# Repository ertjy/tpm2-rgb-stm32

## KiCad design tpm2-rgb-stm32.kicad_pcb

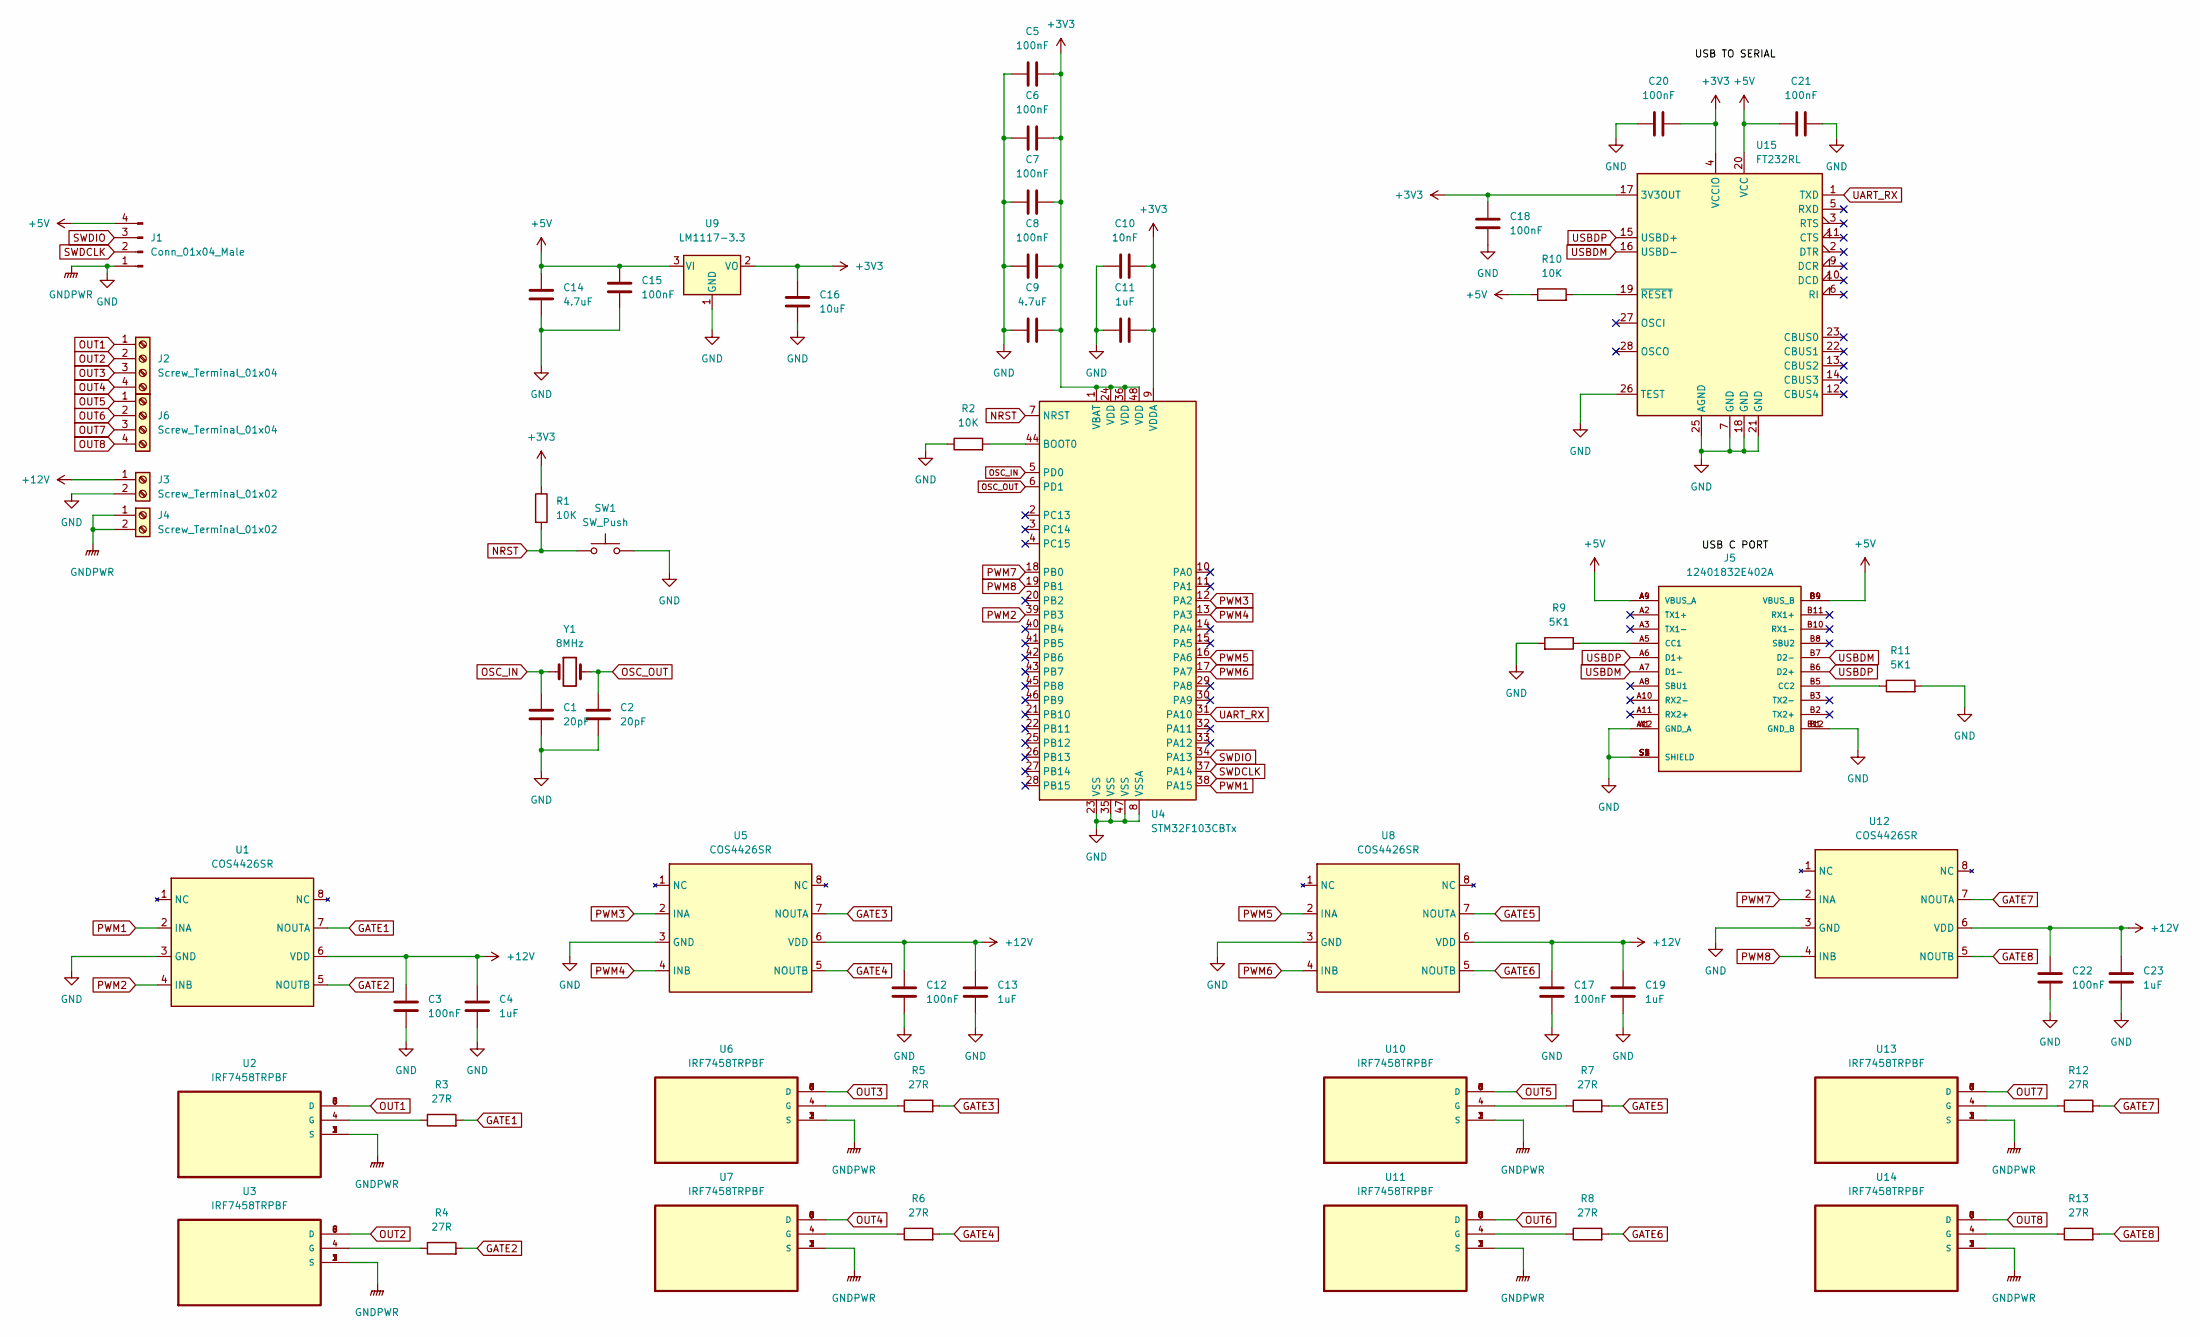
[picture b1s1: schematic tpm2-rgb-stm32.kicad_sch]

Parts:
C1, C2: 20pF; C_0805_2012Metric
C3, C5, C6, C7, C8, C12, C15, C17, C18, C20, C21, C22: 100nF; C_0805_2012Metric
C4, C11, C13, C19, C23: 1uF; C_0805_2012Metric
C9, C14: 4.7uF; C_0805_2012Metric
C10: 10nF; C_0805_2012Metric
C16: 10uF; C_0805_2012Metric
J1: Conn_01x04_Male; PinHeader_1x04_P2.54mm_Vertical
J2, J6: Screw_Terminal_01x04; TerminalBlock_bornier-4_P5.08mm
J3, J4: Screw_Terminal_01x02; TerminalBlock_bornier-2_P5.08mm
J5: 12401832E402A; AMPHENOL_12401832E402A; PARTREV X2
R1, R2, R10: 10K; R_0805_2012Metric
R3, R4, R5, R6, R7, R8, R12, R13: 27R; R_0805_2012Metric
R9, R11: 5K1; R_0805_2012Metric
SW1: SW_Push; SW_147873-1
U1, U5, U8, U12: COS4426SR; SO-8_3.9x4.9mm_P1.27mm
U2, U3, U6, U7, U10, U11, U13, U14: IRF7458TRPBF; SOIC127P490X600X175-8N
U4: STM32F103CBTx; LQFP-48_7x7mm_P0.5mm
U9: LM1117-3.3; SOT-223-3_TabPin2
U15: FT232RL; SSOP-28_5.3x10.2mm_P0.65mm
Y1: 8MHz; Crystal_SMD_HC49-SD

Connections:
+3V3: C5.2, C6.2, C7.2, C8.2, C9.2, C10.2, C11.2, C16.1, C18.1, C20.2, R1.1, U4.1 (VBAT), U4.9 (VDDA), U4.24 (VDD), U4.36 (VDD), U4.48 (VDD), U9.2 (VO), U15.4 (VCCIO), U15.17 (3V3OUT)
+5V: C14.1, C15.1, C21.1, J1.4, J5.A4 (VBUS_A), J5.A9 (VBUS_A), J5.B4 (VBUS_B), J5.B9 (VBUS_B), R10.1, U9.3 (VI), U15.20 (VCC)
+12V: C3.1, C4.1, C12.1, C13.1, C17.1, C19.1, C22.1, C23.1, J3.1, U1.6 (VDD), U5.6 (VDD), U8.6 (VDD), U12.6 (VDD)
GATE1: R3.2, U1.7 (NOUTA)
GATE2: R4.2, U1.5 (NOUTB)
GATE3: R5.2, U5.7 (NOUTA)
GATE4: R6.2, U5.5 (NOUTB)
GATE5: R7.2, U8.7 (NOUTA)
GATE6: R8.2, U8.5 (NOUTB)
GATE7: R12.2, U12.7 (NOUTA)
GATE8: R13.2, U12.5 (NOUTB)
GND: C1.2, C2.2, C3.2, C4.2, C5.1, C6.1, C7.1, C8.1, C9.1, C10.1, C11.1, C12.2, C13.2, C14.2, C15.2, C16.2, C17.2, C18.2, C19.2, C20.1, C21.2, C22.2, C23.2, J1.1, J3.2, J4.1, J4.2, J5.A1 (GND_A), J5.A12 (GND_A), J5.B1 (GND_B), J5.B12 (GND_B), J5.S1 (SHIELD), J5.S2 (SHIELD), J5.S3 (SHIELD), J5.S4 (SHIELD), R2.1, R9.2, R11.2, SW1.2, U1.3 (GND), U2.1 (S), U2.2 (S), U2.3 (S), U3.1 (S), U3.2 (S), U3.3 (S), U4.8 (VSSA), U4.23 (VSS), U4.35 (VSS), U4.47 (VSS), U5.3 (GND), U6.1 (S), U6.2 (S), U6.3 (S), U7.1 (S), U7.2 (S), U7.3 (S), U8.3 (GND), U9.1 (GND), U10.1 (S), U10.2 (S), U10.3 (S), U11.1 (S), U11.2 (S), U11.3 (S), U12.3 (GND), U13.1 (S), U13.2 (S), U13.3 (S), U14.1 (S), U14.2 (S), U14.3 (S), U15.7 (GND), U15.18 (GND), U15.21 (GND), U15.25 (AGND), U15.26 (TEST)
NRST: R1.2, SW1.1, U4.7 (NRST)
unnamed: J5.A5 (CC1), R9.1
unnamed: J5.B5 (CC2), R11.1
unnamed: R2.2, U4.44 (BOOT0)
unnamed: R3.1, U2.4 (G)
unnamed: R4.1, U3.4 (G)
unnamed: R5.1, U6.4 (G)
unnamed: R6.1, U7.4 (G)
unnamed: R7.1, U10.4 (G)
unnamed: R8.1, U11.4 (G)
unnamed: R10.2, U15.19 (~RESET)
unnamed: R12.1, U13.4 (G)
unnamed: R13.1, U14.4 (G)
OSC_IN: C1.1, U4.5 (PD0), Y1.1
OSC_OUT: C2.1, U4.6 (PD1), Y1.2
OUT1: J2.1, U2.5 (D), U2.6 (D), U2.7 (D), U2.8 (D)
OUT2: J2.2, U3.5 (D), U3.6 (D), U3.7 (D), U3.8 (D)
OUT3: J2.3, U6.5 (D), U6.6 (D), U6.7 (D), U6.8 (D)
OUT4: J2.4, U7.5 (D), U7.6 (D), U7.7 (D), U7.8 (D)
OUT5: J6.1, U10.5 (D), U10.6 (D), U10.7 (D), U10.8 (D)
OUT6: J6.2, U11.5 (D), U11.6 (D), U11.7 (D), U11.8 (D)
OUT7: J6.3, U13.5 (D), U13.6 (D), U13.7 (D), U13.8 (D)
OUT8: J6.4, U14.5 (D), U14.6 (D), U14.7 (D), U14.8 (D)
PWM1: U1.2 (INA), U4.38 (PA15)
PWM2: U1.4 (INB), U4.39 (PB3)
PWM3: U4.12 (PA2), U5.2 (INA)
PWM4: U4.13 (PA3), U5.4 (INB)
PWM5: U4.16 (PA6), U8.2 (INA)
PWM6: U4.17 (PA7), U8.4 (INB)
PWM7: U4.18 (PB0), U12.2 (INA)
PWM8: U4.19 (PB1), U12.4 (INB)
SWDCLK: J1.2, U4.37 (PA14)
SWDIO: J1.3, U4.34 (PA13)
UART_RX: U4.31 (PA10), U15.1 (TXD)
USBDM: J5.A7 (D1-), J5.B7 (D2-), U15.16 (USBD-)
USBDP: J5.A6 (D1+), J5.B6 (D2+), U15.15 (USBD+)

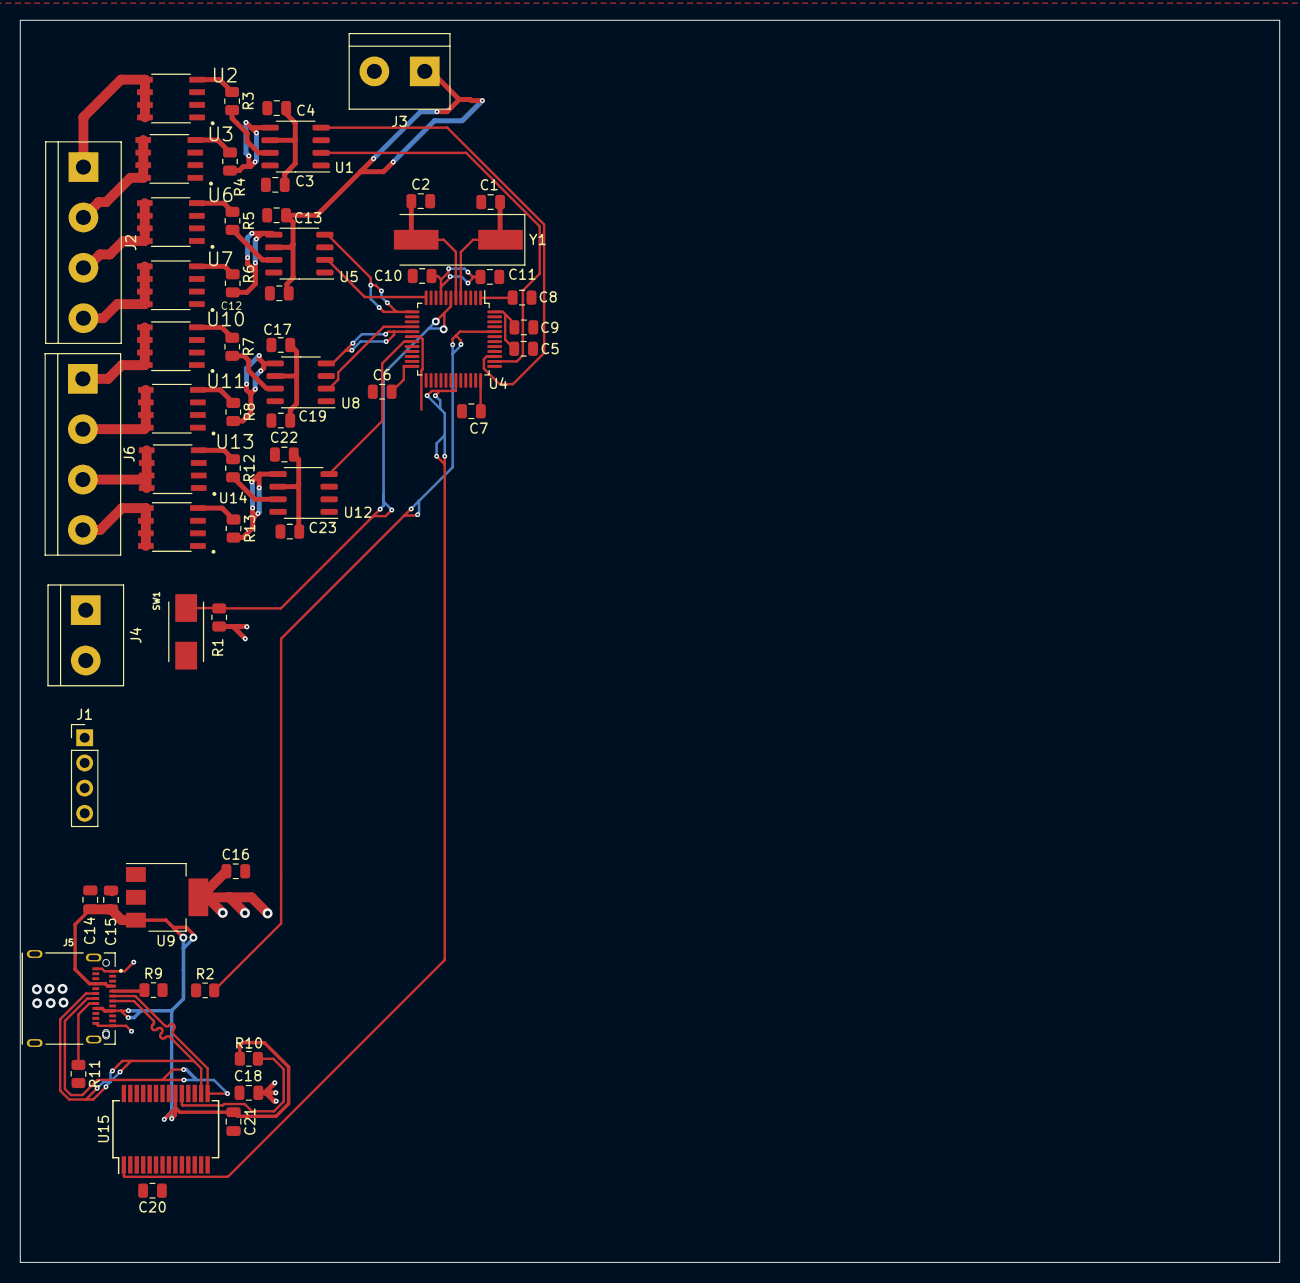
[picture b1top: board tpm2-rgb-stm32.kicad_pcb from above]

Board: 4 copper layers, 127.0 x 125.3 mm, 59 parts (0 on the bottom side), 48 nets.

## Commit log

2023-01-18 Add initial schematic
2023-01-19 added part annotations
2023-01-20 small fixes
2023-01-23 touch ups
2023-01-24 Change folder structure
2023-01-24 Touch things up
2023-01-24 Add missing footprints
2023-01-24 Do initial board setup
2023-01-25 Start layout
2023-01-29 More PCB layout
2023-02-05 Do more routing
2023-02-10 More work
2023-02-10 more routing
2023-02-19 Remove swd traces
